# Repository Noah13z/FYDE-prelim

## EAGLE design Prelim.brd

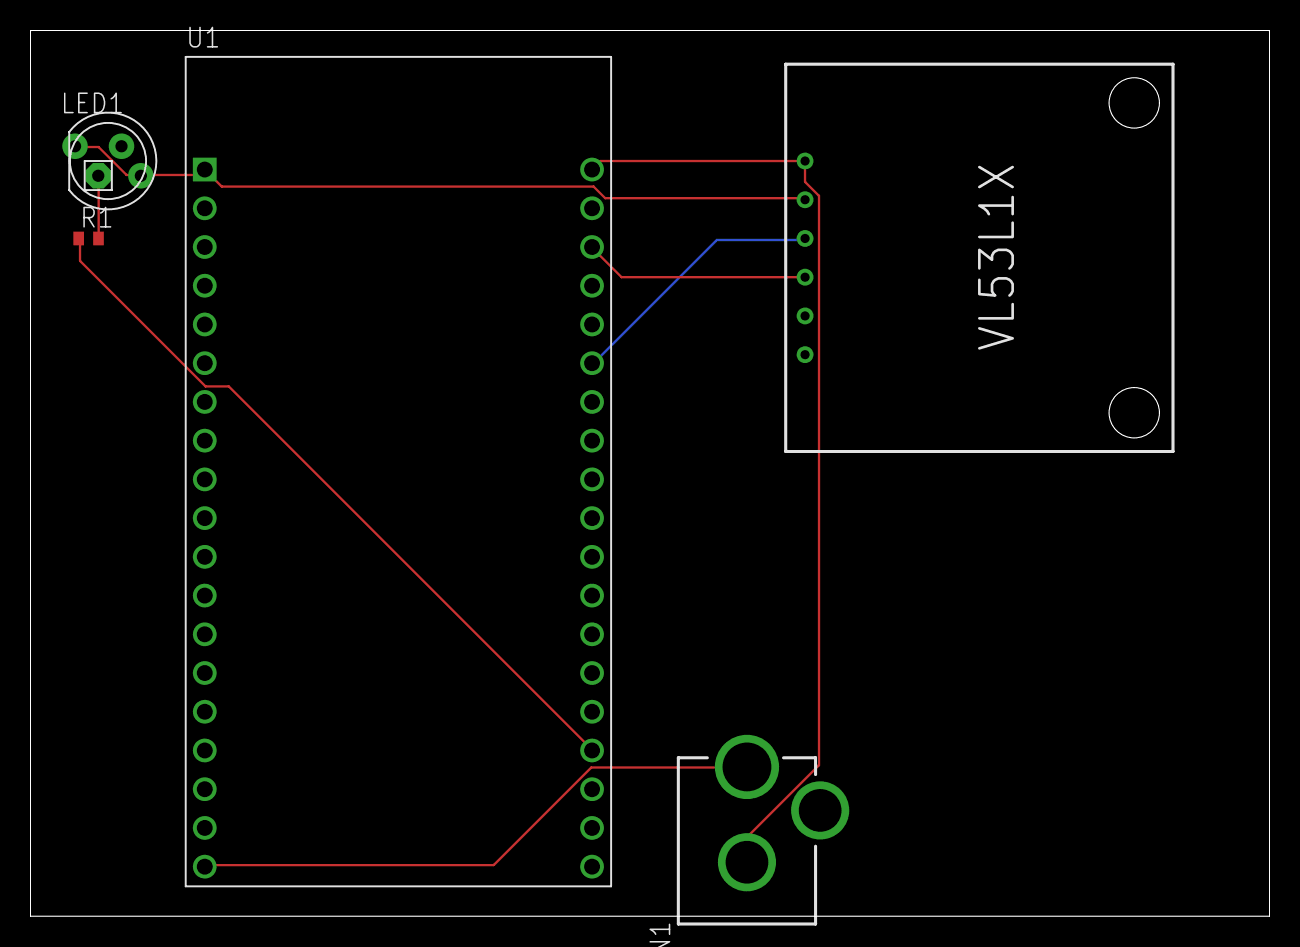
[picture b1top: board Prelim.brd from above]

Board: 2 copper layers, 81.3 x 58.1 mm, 5 parts (0 on the bottom side), 7 nets.

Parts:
CN1: DCJACK_2MM_PTH
LED1: RGBLED_CA-5MM; LED5MMRGB
R1: 10k; R0402
U1: ESP32-DEVKITC-32D; MODULE_ESP32-DEVKITC-32D
U$1: QWIIC_STIANCE_SENSOR_VL53L1X; QWIIC_DISTANCE_SENSOR_VL53L1X

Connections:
+3V3: LED1.1, LED1.4, U1.1, U$1.P$2
GND: CN1.GND, U1.20, U$1.P$1
unnamed: U1.25, U$1.P$3
unnamed: U1.22, U$1.P$4
unnamed: R1.1, U1.35
unnamed: LED1.2, R1.2
unnamed: CN1.PWR, U1.19

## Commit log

2020-04-24 push
2020-04-24 IMPORTANT STUFF
2020-04-24 wired it up
